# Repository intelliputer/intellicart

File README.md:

# Intellicart

Intellicart is an open hardware flash cartridge for the Mattel Intellivision.
It runs on a Teensy 4.1, loads Intellivision cartridge images from a microSD
card, and uses an OLED display plus three cartridge buttons for selection.

## Project status

### Firmware and user interface: current baseline

The current Teensy 4.1 firmware builds with Arduino CLI, uploads successfully,
and has been exercised through the OLED/button interface and microSD browser.
It includes the Intellicart branding, startup help, title-and-publisher browser
view, bidirectional browser wraparound, button-release debouncing, and return
to the last selected game after leaving gameplay.

This is the baseline for future firmware development. Changes to game support,
the user interface, or the bus emulator should be developed and tested against
this firmware independently of physical cartridge assembly.

### Physical cartridge bring-up: pending live test

The remaining hardware milestone is to fit the 74LVC245 bus-transceiver ICs and
perform a live test on an Intellivision console. That test should validate:

- cartridge insertion, power-up, and reset behavior;
- OLED/button operation while installed in the console;
- selection and loading of a known-good standard ROM from microSD;
- controller operation, game reset, and return to the browser;
- reliable bus behavior before testing mapper-specific titles.

Treat any issues found during the live test as hardware-integration findings,
not regressions in the verified firmware baseline, unless the evidence points
to the firmware.

### Bus-transceiver requirement

Fit **74LVC245 or 74LVC245A** parts in U1, U2, U3, and U5. The board is a
3.3 V Teensy interface to a 5 V Intellivision cartridge bus: the LVC family
operates from the board's 3.3 V rail and has 5-V-tolerant bus inputs. Its 3.3 V
outputs are valid logic highs for the console's TTL-style inputs.

Do **not** substitute 74LS245 devices. They require a 4.75--5.25 V supply and
are therefore out of specification on this board. Supplying them at 5 V would
also allow their outputs to drive Teensy-connected signals at unsafe 5 V logic
levels. This is especially important for U1/U2's bidirectional 16-bit bus and
U3's console-to-Teensy control signals.

The supplied [SN74LVC245A datasheet](board/74lvc245a.pdf) documents the
3.3 V operating range and 5.5 V input tolerance. The included
[SN74LS245 datasheet](board/74ls245.pdf) documents its 5 V supply requirement.

## Firmware

The Arduino sketch is
[`development/teensy/intellicart/intellicart.ino`](development/teensy/intellicart/intellicart.ino).

### Requirements

- Arduino CLI or Arduino IDE with the **Teensy 4.1** board package installed.
- The PJRC Teensy Boards Manager URL:
  `https://www.pjrc.com/teensy/package_teensy_index.json`
- Arduino libraries:
  - `Adafruit GFX Library`
  - `Adafruit SSD1306`

Do **not** install a generic `SdFat` library through Arduino Library Manager.
Intellicart uses Teensy's bundled, SDIO-compatible SdFat implementation via
`SD.h`.

### Build and upload with Arduino CLI

```bash
arduino-cli config add board_manager.additional_urls \
  https://www.pjrc.com/teensy/package_teensy_index.json
arduino-cli core update-index
arduino-cli core install teensy:avr
arduino-cli lib install "Adafruit GFX Library" "Adafruit SSD1306"

arduino-cli compile --upload \
  --fqbn teensy:avr:teensy41 \
  --port <teensy-port> \
  development/teensy/intellicart
```

Find the current Teensy port with:

```bash
arduino-cli board list
```

On Linux, install PJRC's udev rule before uploading as a non-root user. See
the [Teensy 4.1 documentation](https://www.pjrc.com/store/teensy41.html).

## Preparing the microSD card

Use a 1--32 GB microSD card formatted as FAT or FAT32. Put the fallback
configuration below in the card root as `0.cfg`:

```ini
[mapping]
$0000 - $1FFF = $5000 ; 8K to $5000 - $6FFF
$2000 - $2FFF = $D000 ; 4K to $D000 - $DFFF
$3000 - $3FFF = $F000 ; 4K to $F000 - $FFFF
```

Copy legally obtained Intellivision game dumps as `.bin` files. A game can
have a same-named `.cfg` file for its specific memory mapping:

```text
SD_CARD/
├── 0.cfg
├── Pitfall.bin
├── Pitfall.cfg
├── Astrosmash.bin
└── Astrosmash.cfg
```

`0.cfg` is used when no same-named CFG is present. It supports many standard
ROMs, but bank-switched or RAM-mapped titles may require their own CFG file.
The browser only displays `.bin` files; CFG files remain hidden.

Files may be stored in the root or a root-level folder. Keep names below 45
characters and avoid unusual punctuation. `.int` images use the same binary
format and may be renamed to `.bin`; `.rom` images must first be converted to
BIN plus CFG.

## Current SD-card catalogue

[`catalog/SD-CARD-CATALOG.md`](catalog/SD-CARD-CATALOG.md) records every
numbered image on the prepared `INTELLICART` card, including its source title,
year, publisher, category, byte size, and exact card filename. It is intended
as the reference for later compatibility and mapper testing. The catalogue
also supports local cover thumbnails in `catalog/covers/`, using a three-digit
catalogue number such as `053.png`.

## Controls

At startup, pressing any cartridge button opens the browser. The OLED shows:

```text
          Intellicart
PB1/PB3: Navigate
PB2: Start
PB3: Menu
```

| Context | PB1 | PB2 | PB3 |
| --- | --- | --- | --- |
| Browser | Next item | Open folder / start game | Previous item |
| Game running | Restart current game | — | Return to browser |

Browser navigation wraps in both directions. Returning to the browser from a
game restores the previously selected game and directory. The browser displays
a game title and publisher when the filename encodes them; otherwise it shows
the title and file size. Long display text is shortened with an ellipsis.

The small centre button on the Teensy 4.1 is a **Program** button, not a game
reset button. It enters Teensy's bootloader for firmware recovery/uploading.
Do not hold it for 13--17 seconds: that restores the default Teensy blink
program and erases the Intellicart firmware.

## Repository layout

| Path | Contents |
| --- | --- |
| [`board/project/`](board/project/) | KiCad schematic, PCB, project configuration, routing, and BOM files. |
| [`board/manufacturing/`](board/manufacturing/) | Controlled fabrication procedure, draft packages, and release records. |
| [`development/teensy/intellicart/`](development/teensy/intellicart/) | Teensy 4.1 firmware and startup ROM image. |
| [`development/checkers-disassembly/`](development/checkers-disassembly/) | CP1610 disassembly and analysis workspace for the Checkers ROM. |
| [`catalog/`](catalog/) | Current SD-card inventory, optional cover artwork, and test reference. |
| [`scripts/generate_sd_catalog.py`](scripts/generate_sd_catalog.py) | Rebuilds the SD-card catalogue from the card and source ROM set. |
| [`manual/`](manual/) | User manual source, assets, and compiled PDF. |
| [`rom/`](rom/) | ROM images used for development and research. |

## Hardware and manual

The KiCad project is
[`board/project/intellicart.kicad_pro`](board/project/intellicart.kicad_pro).

The stale 2026-10-05 Gerber export has been removed. The current
[`Intellicart r1.3 draft`](board/manufacturing/Intellicart-Gerbers-r1.3-draft/)
is suitable for manufacturer fitness review only, not ordering. Follow the
release gate in [`board/manufacturing/README.md`](board/manufacturing/README.md)
before declaring a production revision.

The editable user-manual source is [`manual/UserManual.tex`](manual/UserManual.tex).
To rebuild its PDF:

```bash
cd manual
latexmk -pdf UserManual.tex
```

## Licensing and ROMs

The hardware and project files are provided under the repository's
[license](LICENSE). ROM images may be subject to their own rights; use and
distribute them only where you have the appropriate authorization.

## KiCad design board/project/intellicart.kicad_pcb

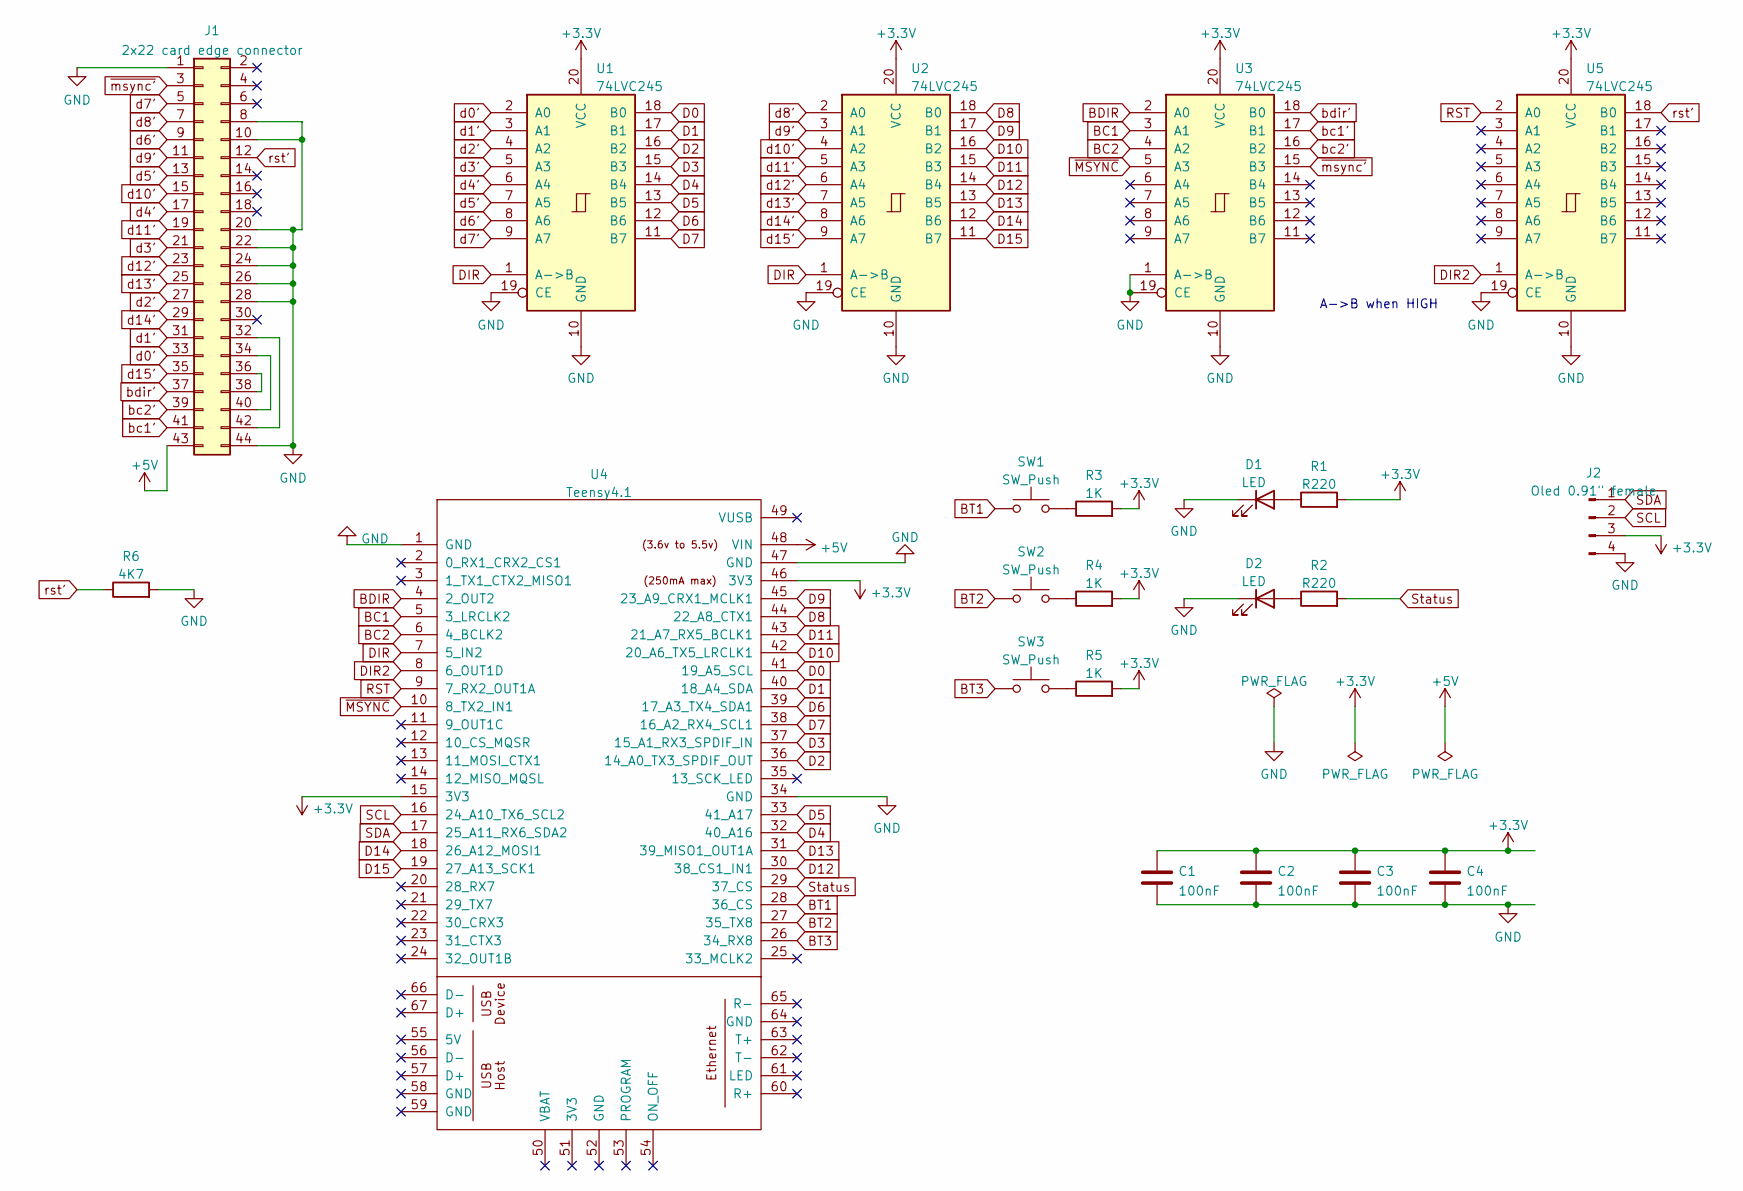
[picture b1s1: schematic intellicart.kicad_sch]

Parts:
C1, C2, C3, C4: 100nF; C_Disc_D3.8mm_W2.6mm_P2.50mm
D1, D2: LED; LED_D3.0mm
J1: 2x22 card edge connector; edge mounted 44 pin card edge connector (2x22 pin)
J2: Oled 0.91" female; PinHeader_1x04_P2.54mm_Vertical
R1, R2: R220; R_Axial_DIN0204_L3.6mm_D1.6mm_P7.62mm_Horizontal
R3, R4, R5: 1K; R_Axial_DIN0204_L3.6mm_D1.6mm_P7.62mm_Horizontal
R6: 4K7; R_Axial_DIN0204_L3.6mm_D1.6mm_P7.62mm_Horizontal
SW1, SW2, SW3: SW_Push; SW_PUSH_6mm
U1, U2, U3, U5: 74LVC245; DIP-20_W7.62mm_Socket
U4: Teensy4.1; Teensy41

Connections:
+3.3V: C1.1, C2.1, C3.1, C4.1, J2.3, R1.2, R3.2, R4.2, R5.2, U1.20 (VCC), U2.20 (VCC), U3.20 (VCC), U4.15 (3V3), U4.46 (3V3), U5.20 (VCC)
+5V: J1.43, U4.48 (VIN)
BC1: U3.3 (A1), U4.5 (3_LRCLK2)
BC2: U3.4 (A2), U4.6 (4_BCLK2)
BDIR: U3.2 (A0), U4.4 (2_OUT2)
BT1: SW1.1, U4.28 (36_CS)
BT2: SW2.1, U4.27 (35_TX8)
BT3: SW3.1, U4.26 (34_RX8)
D0: U1.18 (B0), U4.41 (19_A5_SCL)
D1: U1.17 (B1), U4.40 (18_A4_SDA)
D2: U1.16 (B2), U4.36 (14_A0_TX3_SPDIF_OUT)
D3: U1.15 (B3), U4.37 (15_A1_RX3_SPDIF_IN)
D4: U1.14 (B4), U4.32 (40_A16)
D5: U1.13 (B5), U4.33 (41_A17)
D6: U1.12 (B6), U4.39 (17_A3_TX4_SDA1)
D7: U1.11 (B7), U4.38 (16_A2_RX4_SCL1)
D8: U2.18 (B0), U4.44 (22_A8_CTX1)
D9: U2.17 (B1), U4.45 (23_A9_CRX1_MCLK1)
D10: U2.16 (B2), U4.42 (20_A6_TX5_LRCLK1)
D11: U2.15 (B3), U4.43 (21_A7_RX5_BCLK1)
D12: U2.14 (B4), U4.30 (38_CS1_IN1)
D13: U2.13 (B5), U4.31 (39_MISO1_OUT1A)
D14: U2.12 (B6), U4.18 (26_A12_MOSI1)
D15: U2.11 (B7), U4.19 (27_A13_SCK1)
DIR: U1.1 (A->B), U2.1 (A->B), U4.7 (5_IN2)
DIR2: U4.8 (6_OUT1D), U5.1 (A->B)
GND: C1.2, C2.2, C3.2, C4.2, D1.1 (K), D2.1 (K), J1.1, J1.8, J1.10, J1.20, J1.22, J1.24, J1.26, J1.28, J1.44, J2.4, R6.2, U1.10 (GND), U1.19 (CE), U2.10 (GND), U2.19 (CE), U3.1 (A->B), U3.10 (GND), U3.19 (CE), U4.1 (GND), U4.34 (GND), U4.47 (GND), U5.10 (GND), U5.19 (CE)
unnamed: D1.2 (A), R1.1
unnamed: D2.2 (A), R2.1
unnamed: J1.32, J1.42
unnamed: J1.34, J1.40
unnamed: J1.36, J1.38
unnamed: R3.1, SW1.2
unnamed: R4.1, SW2.2
unnamed: R5.1, SW3.2
RST: U4.9 (7_RX2_OUT1A), U5.2 (A0)
SCL: J2.2, U4.16 (24_A10_TX6_SCL2)
SDA: J2.1, U4.17 (25_A11_RX6_SDA2)
Status: R2.2, U4.29 (37_CS)
bc1': J1.41, U3.17 (B1)
bc2': J1.39, U3.16 (B2)
bdir': J1.37, U3.18 (B0)
d0': J1.33, U1.2 (A0)
d1': J1.31, U1.3 (A1)
d2': J1.27, U1.4 (A2)
d3': J1.21, U1.5 (A3)
d4': J1.17, U1.6 (A4)
d5': J1.13, U1.7 (A5)
d6': J1.9, U1.8 (A6)
d7': J1.5, U1.9 (A7)
d8': J1.7, U2.2 (A0)
d9': J1.11, U2.3 (A1)
d10': J1.15, U2.4 (A2)
d11': J1.19, U2.5 (A3)
d12': J1.23, U2.6 (A4)
d13': J1.25, U2.7 (A5)
d14': J1.29, U2.8 (A6)
d15': J1.35, U2.9 (A7)
rst': J1.12, R6.1, U5.18 (B0)
~MSYNC: U3.5 (A3), U4.10 (8_TX2_IN1)
~msync': J1.3, U3.15 (B3)

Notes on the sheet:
A->B when HIGH

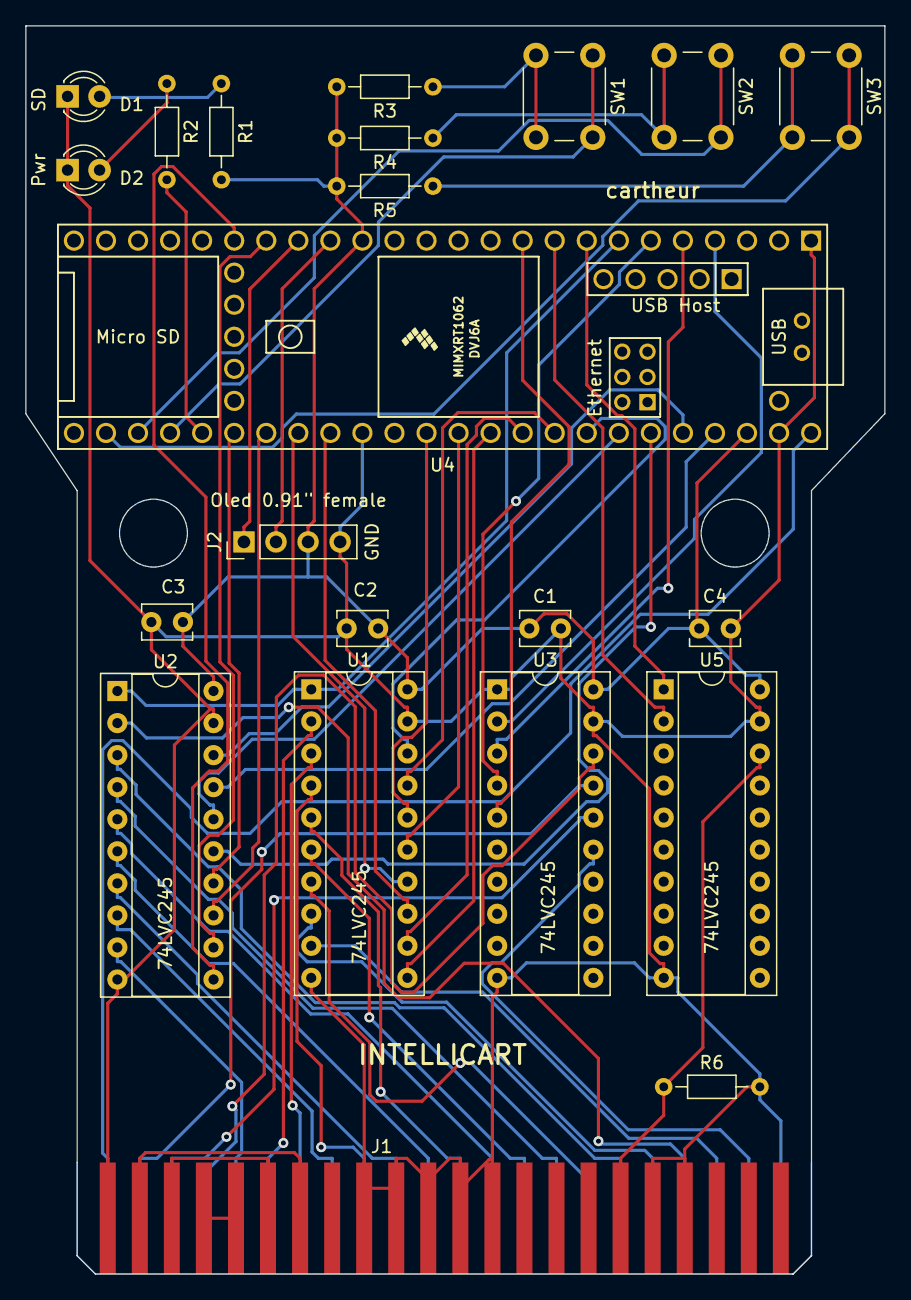
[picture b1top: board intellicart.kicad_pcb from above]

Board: 2 copper layers, 68.1 x 98.9 mm, 22 parts (0 on the bottom side), 61 nets.

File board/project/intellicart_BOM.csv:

Column1,Column2,Column3,Column4,Column5,Column6,Column7
Component Count:,22,,,,,
,,,,,,
Individual Components:,,,,,,
,,,,,,
Item,Qty,Reference(s),Value,LibPart,Footprint,Datasheet
,,C1,100nF,Device:C,Capacitor_THT:C_Disc_D3.8mm_W2.6mm_P2.50mm,~
,,C2,100nF,Device:C,Capacitor_THT:C_Disc_D3.8mm_W2.6mm_P2.50mm,~
,,C3,100nF,Device:C,Capacitor_THT:C_Disc_D3.8mm_W2.6mm_P2.50mm,~
,,C4,100nF,Device:C,Capacitor_THT:C_Disc_D3.8mm_W2.6mm_P2.50mm,~
,,D1,LED,Device:LED,LED_THT:LED_D3.0mm,~
,,D2,LED,Device:LED,LED_THT:LED_D3.0mm,~
,,J2,"Oled 0.91"" female",Connector:Conn_01x04_Male,Connector_PinHeader_2.54mm:PinHeader_1x04_P2.54mm_Vertical,~
,,R1,R220,Device:R,Resistor_THT:R_Axial_DIN0204_L3.6mm_D1.6mm_P7.62mm_Horizontal,~
,,R2,R220,Device:R,Resistor_THT:R_Axial_DIN0204_L3.6mm_D1.6mm_P7.62mm_Horizontal,~
,,R3,1K,Device:R,Resistor_THT:R_Axial_DIN0204_L3.6mm_D1.6mm_P7.62mm_Horizontal,~
,,R4,1K,Device:R,Resistor_THT:R_Axial_DIN0204_L3.6mm_D1.6mm_P7.62mm_Horizontal,~
,,R5,1K,Device:R,Resistor_THT:R_Axial_DIN0204_L3.6mm_D1.6mm_P7.62mm_Horizontal,~
,,R6,4K7,Device:R,Resistor_THT:R_Axial_DIN0204_L3.6mm_D1.6mm_P7.62mm_Horizontal,~
,,SW1,SW_Push,Switch:SW_Push,Button_Switch_THT:SW_PUSH_6mm,~
,,SW2,SW_Push,Switch:SW_Push,Button_Switch_THT:SW_PUSH_6mm,~
,,SW3,SW_Push,Switch:SW_Push,Button_Switch_THT:SW_PUSH_6mm,~
,,U1,74LVC245,74xx:74LS245,Package_DIP:DIP-20_W7.62mm_Socket,http://www.ti.com/lit/gpn/sn74LS245
,,U2,74LVC245,74xx:74LS245,Package_DIP:DIP-20_W7.62mm_Socket,http://www.ti.com/lit/gpn/sn74LS245
,,U3,74LVC245,74xx:74LS245,Package_DIP:DIP-20_W7.62mm_Socket,http://www.ti.com/lit/gpn/sn74LS245
,,U4,Teensy4.1,teensy:Teensy4.1,Teensy:Teensy41,
,,U5,74LVC245,74xx:74LS245,Package_DIP:DIP-20_W7.62mm_Socket,http://www.ti.com/lit/gpn/sn74LS245
,,,,,,
,,,,,,
,,,,,,
Collated Components:,,,,,,
,,,,,,
Item,Qty,Reference(s),Value,LibPart,Footprint,Datasheet
1,4,"C1, C2, C3, C4",100nF,Device:C,Capacitor_THT:C_Disc_D3.8mm_W2.6mm_P2.50mm,~
2,2,"D1, D2",LED,Device:LED,LED_THT:LED_D3.0mm,~
3,1,J1,2x22 card edge connector,Evan's misc parts:2x22 card edge connector,Evan's misc parts:edge mounted 44 pin card edge connector (2x22 pin),~
4,1,J2,"Oled 0.91"" female",Connector:Conn_01x04_Male,Connector_PinHeader_2.54mm:PinHeader_1x04_P2.54mm_Vertical,~
5,2,"R1, R2",R220,Device:R,Resistor_THT:R_Axial_DIN0204_L3.6mm_D1.6mm_P7.62mm_Horizontal,~
6,3,"R3, R4, R5",1K,Device:R,Resistor_THT:R_Axial_DIN0204_L3.6mm_D1.6mm_P7.62mm_Horizontal,~
7,1,R6,4K7,Device:R,Resistor_THT:R_Axial_DIN0204_L3.6mm_D1.6mm_P7.62mm_Horizontal,~
8,3,"SW1, SW2, SW3",SW_Push,Switch:SW_Push,Button_Switch_THT:SW_PUSH_6mm,~
9,4,"U1, U2, U3, U5",74LVC245,74xx:74LS245,Package_DIP:DIP-20_W7.62mm_Socket,http://www.ti.com/lit/gpn/sn74LS245
10,1,U4,Teensy4.1,teensy:Teensy4.1,Teensy:Teensy41,

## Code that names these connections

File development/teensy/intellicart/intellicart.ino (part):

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
int D_PIN[] ={19,18,14,15,40,41,17,16,22,23,20,21,38,39,26,27};

#define BDIR_PIN  2 //GPIO4_4
#define BC1_PIN   3 //GPIO4_5
#define BC2_PIN   4 //GPIO4_6
#define DIR_PIN   5 //GPIO4_8 - TO PIN 1 LVC245, HIGH= A->B (INPUT 5V TO 3.3V) LOW= B->A (OUTPUT 3.3V TO 5V)
#define DIR2_PIN  6 //GPIO2_10 - TO PIN 1 LVC245, HIGH= A->B (INPUT 5V TO 3.3V) LOW= B->A (OUTPUT 3.3V TO 5V)
#define BT2_PIN  35 //GPIO2_26
#define BT1_PIN  36 //GPIO2_28
#define BT3_PIN  34 //GPIO2_29
#define Status_PIN   37 //GPIO2_19
#define RST_PIN   7 //GPIO2_17
#define MSYNC_PIN   8 //GPIO2_16

// Inty bus values (BC2+BC1+BDIR)
#define BUS_NACT  0b000  //0
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  IOMUXC_SW_MUX_CTL_PAD_GPIO_AD_B1_14 = MUX;
  IOMUXC_SW_MUX_CTL_PAD_GPIO_AD_B1_15 = MUX;

  IOMUXC_SW_MUX_CTL_PAD_GPIO_EMC_04 = MUX; //GPIO4_4  BDIR
  IOMUXC_SW_MUX_CTL_PAD_GPIO_EMC_05 = MUX; //GPIO4_5  BC1
  IOMUXC_SW_MUX_CTL_PAD_GPIO_EMC_06 = MUX; //GPIO4_6  BC2

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  pinMode(BT1_PIN,INPUT_PULLDOWN);
  pinMode(BT2_PIN,INPUT_PULLDOWN);
  pinMode(BT3_PIN,INPUT_PULLDOWN);
  pinMode(DIR2_PIN,OUTPUT);
  pinMode(RST_PIN,OUTPUT);
  pinMode(MSYNC_PIN,INPUT_PULLDOWN);

  digitalWriteFast(RST_PIN,LOW);   //???????????
  digitalWriteFast(DIR2_PIN,HIGH); // A->B, TEENSY to INTV BUS

  for (long i=0; i<BINLENGTH; i++) {
    ROM[i]=0;
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void resetCart() {

  digitalWriteFast(Status_PIN,HIGH);
  Serial.println(digitalReadFast(MSYNC_PIN));

  do {
    digitalWriteFast(Status_PIN,digitalReadFast(MSYNC_PIN));
    digitalWriteFast(RST_PIN,HIGH);
    delay(6);
    if (digitalReadFast(MSYNC_PIN)==0) break;
    digitalWriteFast(RST_PIN,LOW);
    delay(2);
    if (digitalReadFast(MSYNC_PIN)==0) break;

  } while (digitalReadFast(MSYNC_PIN)==1);

//  do {
   digitalWriteFast(Status_PIN,digitalReadFast(MSYNC_PIN));
   digitalWriteFast(RST_PIN,LOW);
 // } while (digitalReadFast(MSYNC_PIN)==0);


  Serial.println(digitalReadFast(MSYNC_PIN));

  digitalWriteFast(Status_PIN,LOW);
   //pinMode(RST_PIN,INPUT);
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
